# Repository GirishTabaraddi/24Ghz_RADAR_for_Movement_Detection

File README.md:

# 24Ghz_RADAR_for_Movement_Detection

This Project describes the Movement Detection using 24GHz CW-RADAR sensor which was performed in the System Driven Hardware Design Lab as a lab group.

KiCad_LabProject - This folder contains all the schematic and pcb files.
				 - 10_work folder contains the recent files of the project schematic.
				 - 20_release folder contains all the previous versions of the circuit design.

SDHD_PSoC_Codes - This folder contains all the project codes for various lab assigments and final code of the movement detector Project

SDHD_Lab3_FFT.cydsn - This workspace inside the SDHD_PSoC_Codes is the main code required for executing the Movement Detection.

Project Report pdf and ppt are added for reference to understand how the project was performed in the lab during summer semester.

This Project was carried at Hochschule Darmstadt during Summer semester 2023.
Other contributors are: Drashti Shah and Ananya Harish.

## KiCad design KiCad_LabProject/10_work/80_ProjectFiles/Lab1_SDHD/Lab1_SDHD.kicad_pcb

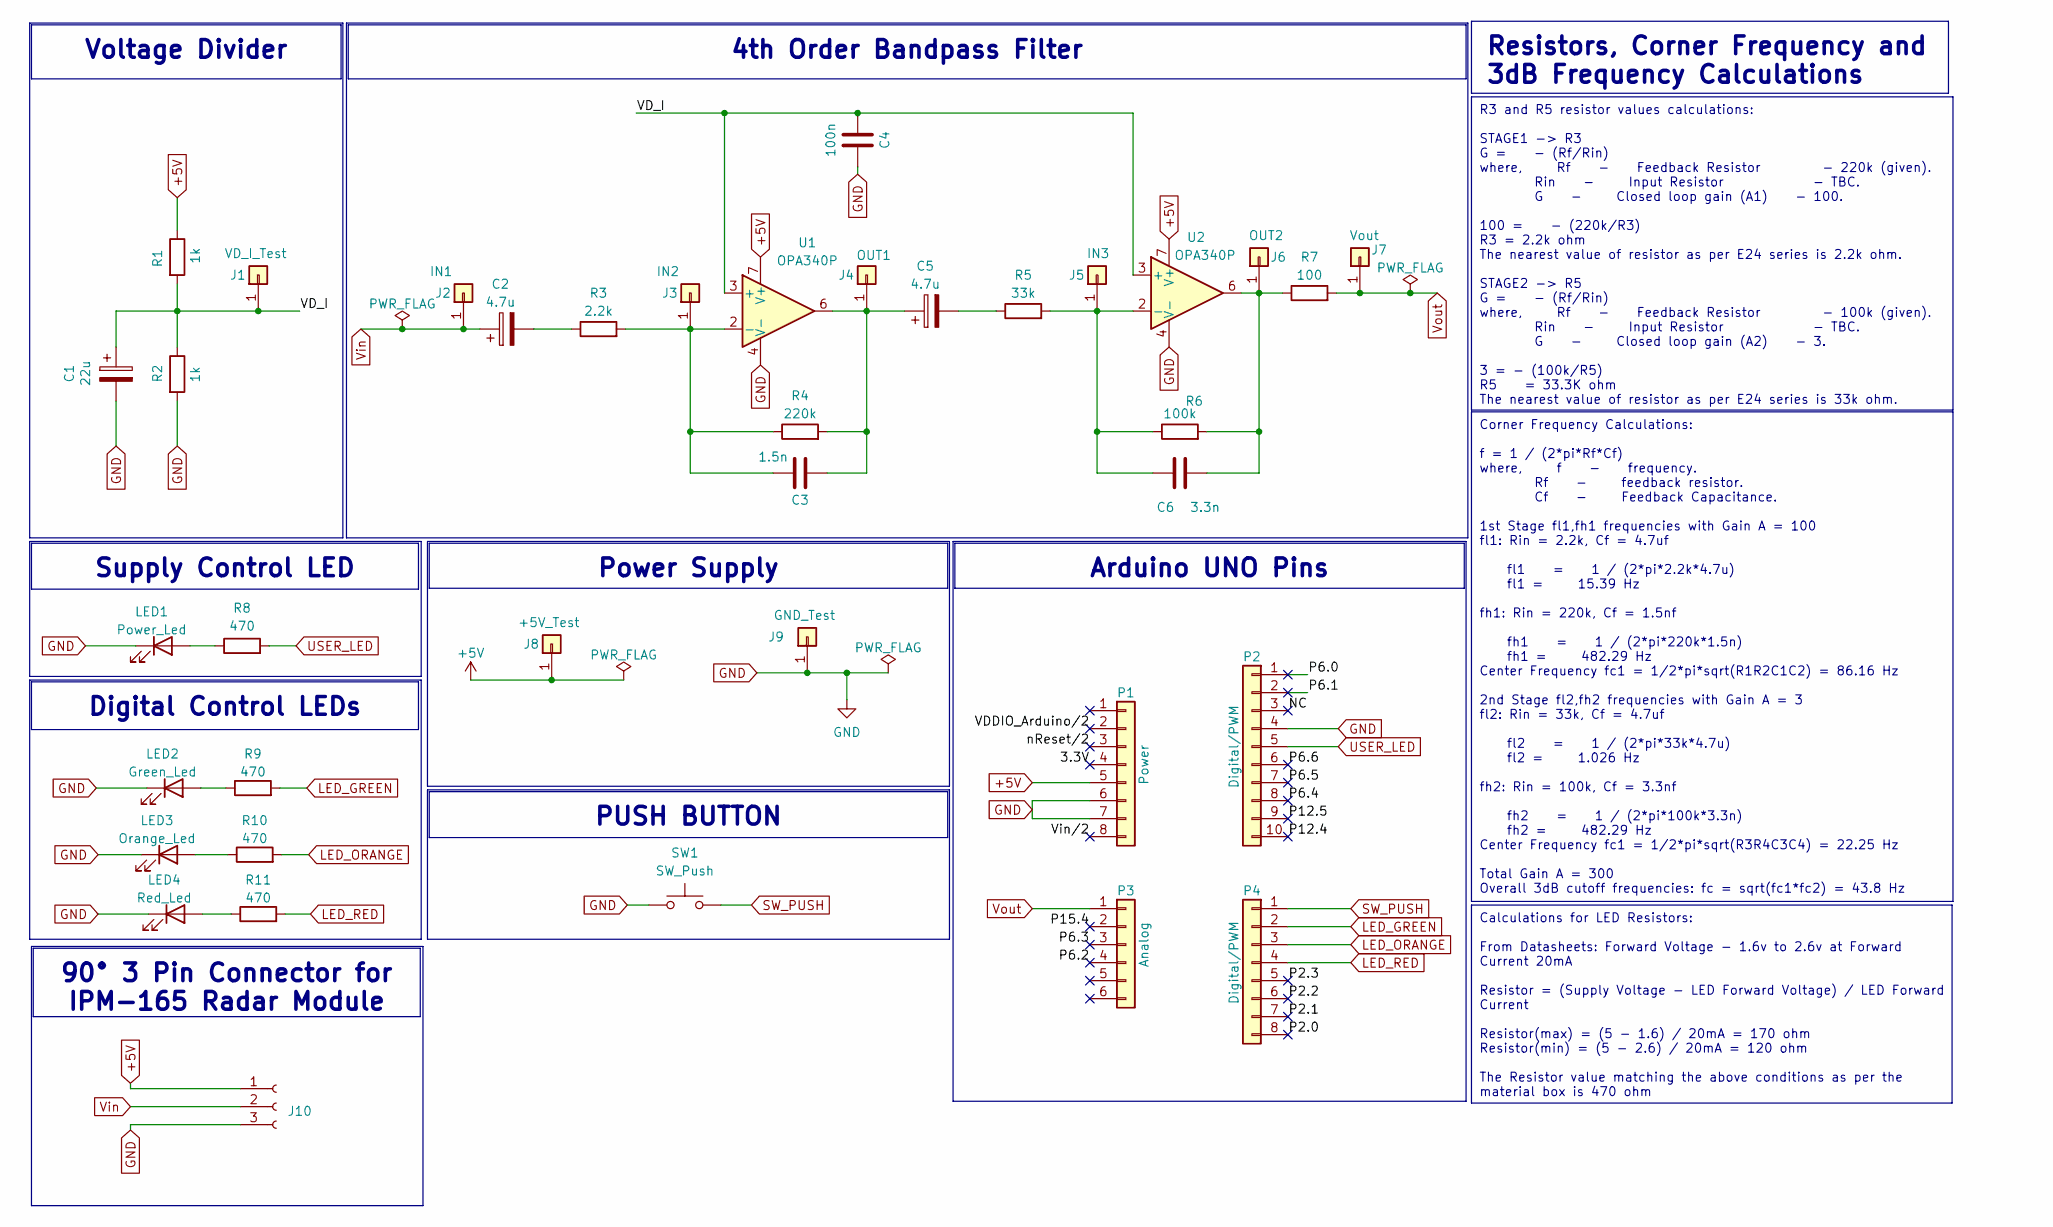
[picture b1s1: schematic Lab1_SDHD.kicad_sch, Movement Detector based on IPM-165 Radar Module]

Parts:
C1: 22u; CP_Radial_D5.0mm_P2.50mm
C2, C5: 4.7u; CP_Radial_D6.3mm_P2.50mm
C3: 1.5n; C_Rect_L7.2mm_W7.2mm_P5.00mm_FKS2_FKP2_MKS2_MKP2
C4: 100n; C_Rect_L7.2mm_W2.5mm_P5.00mm_FKS2_FKP2_MKS2_MKP2
C6: 3.3n; C_Rect_L7.2mm_W7.2mm_P5.00mm_FKS2_FKP2_MKS2_MKP2
J1: VD_I_Test; PinHeader_1x01_P2.54mm_Vertical
J2: IN1; PinHeader_1x01_P2.54mm_Vertical
J3: IN2; PinHeader_1x01_P2.54mm_Vertical
J4: OUT1; PinHeader_1x01_P2.54mm_Vertical
J5: IN3; PinHeader_1x01_P2.54mm_Vertical
J6: OUT2; PinHeader_1x01_P2.54mm_Vertical
J7: Vout; PinHeader_1x01_P2.54mm_Vertical
J8: +5V_Test; PinHeader_1x01_P2.54mm_Vertical
J9: GND_Test; PinHeader_1x01_P2.54mm_Vertical
J10: Conn_01x03_Socket; PinSocket_1x03_P2.54mm_Horizontal_NEW
LED1: Power_Led; LED_D5.0mm
LED2: Green_Led; LED_D5.0mm
LED3: Orange_Led; LED_D5.0mm
LED4: Red_Led; LED_D5.0mm
P1: Power; PinHeader_1x08_P2.54mm_Vertical
P2: Digital/PWM; PinHeader_1x10_P2.54mm_Vertical
P3: Analog; PinHeader_1x06_P2.54mm_Vertical
P4: Digital/PWM; PinHeader_1x08_P2.54mm_Vertical_New
R1, R2: 1k; R_Axial_DIN0207_L6.3mm_D2.5mm_P10.16mm_Horizontal
R3: 2.2k; R_Axial_DIN0207_L6.3mm_D2.5mm_P10.16mm_Horizontal
R4: 220k; R_Axial_DIN0207_L6.3mm_D2.5mm_P10.16mm_Horizontal
R5: 33k; R_Axial_DIN0207_L6.3mm_D2.5mm_P10.16mm_Horizontal
R6: 100k; R_Axial_DIN0207_L6.3mm_D2.5mm_P10.16mm_Horizontal
R7: 100; R_Axial_DIN0207_L6.3mm_D2.5mm_P10.16mm_Horizontal
R8, R9, R10, R11: 470; R_Axial_DIN0207_L6.3mm_D2.5mm_P10.16mm_Horizontal
SW1: SW_Push; SW_PUSH_6mm_H7.3mm
U1, U2: OPA340P; DIP-8_W7.62mm_Socket

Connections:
+5V: J8.1, J10.1, P1.5, R1.1, U1.7 (V+), U2.7 (V+)
/3.3V: P1.4
/NC: P2.3
/P2.0: P4.8
/P2.1: P4.7
/P2.2: P4.6
/P2.3: P4.5
/P6.0: P2.1
/P6.1: P2.2
/P6.2: P3.4
/P6.3: P3.3
/P6.4: P2.8
/P6.5: P2.7
/P6.6: P2.6
/P12.4: P2.10
/P12.5: P2.9
/P15.4: P3.2
/VDDIO_Arduino/2: P1.2
/VD_I: C1.1, C4.2, J1.1, R1.2, R2.1, U1.3 (+), U2.3 (+)
/Vin/2: P1.8
/nReset/2: P1.3
GND: C1.2, C4.1, J9.1, J10.3, LED1.1 (K), LED2.1 (K), LED3.1 (K), LED4.1 (K), P1.6, P1.7, P2.4, R2.2, SW1.1, U1.4 (V-), U2.4 (V-)
LED_GREEN: P4.2, R9.2
LED_ORANGE: P4.3, R10.2
LED_RED: P4.4, R11.2
unnamed: C2.2, R3.1
unnamed: C5.2, R5.1
unnamed: C3.1, J3.1, R3.2, R4.1, U1.2 (-)
unnamed: C3.2, C5.1, J4.1, R4.2, U1.6
unnamed: C6.1, J5.1, R5.2, R6.1, U2.2 (-)
unnamed: C6.2, J6.1, R6.2, R7.1, U2.6
unnamed: LED1.2 (A), R8.1
unnamed: LED2.2 (A), R9.1
unnamed: LED3.2 (A), R10.1
unnamed: LED4.2 (A), R11.1
SW_PUSH: P4.1, SW1.2
USER_LED: P2.5, R8.2
Vin: C2.1, J2.1, J10.2
Vout: J7.1, P3.1, R7.2

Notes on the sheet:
Power Supply
90° 3 Pin Connector for IPM-165 Radar Module
R3 and R5 resistor values calculations: STAGE1 -> R3 G = - (Rf/Rin) where, Rf - Feedback Resistor - 220k (given). Rin - Input Resistor - TBC. G - Closed loop gain (A1) - 100. 100 = - (220k/R3) R3 = 2.2k ohm The nearest value of resistor as per E24 series is 2.2k ohm. STAGE2 -> R5 G = - (Rf/Rin) whe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
Arduino UNO Pins
Corner Frequency Calculations: f = 1 / (2*pi*Rf*Cf) where, f - frequency. Rf - feedback resistor. Cf - Feedback Capacitance. 1st Stage fl1,fh1 frequencies with Gain A = 100 fl1: Rin = 2.2k, Cf = 4.7uf fl1 = 1 / (2*pi*2.2k*4.7u) fl1 = 15.39 Hz fh1: Rin = 220k, Cf = 1.5nf fh1 = 1 / (2*pi*220k*1.5n) f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
Calculations for LED Resistors: From Datasheets: Forward Voltage - 1.6v to 2.6v at Forward Current 20mA Resistor = (Supply Voltage - LED Forward Voltage) / LED Forward Current Resistor(max) = (5 - 1.6) / 20mA = 170 ohm Resistor(min) = (5 - 2.6) / 20mA = 120 ohm The Resistor value matching the above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
4th Order Bandpass Filter
Voltage Divider
Resistors, Corner Frequency and 3dB Frequency Calculations
Supply Control LED
Digital Control LEDs
PUSH BUTTON

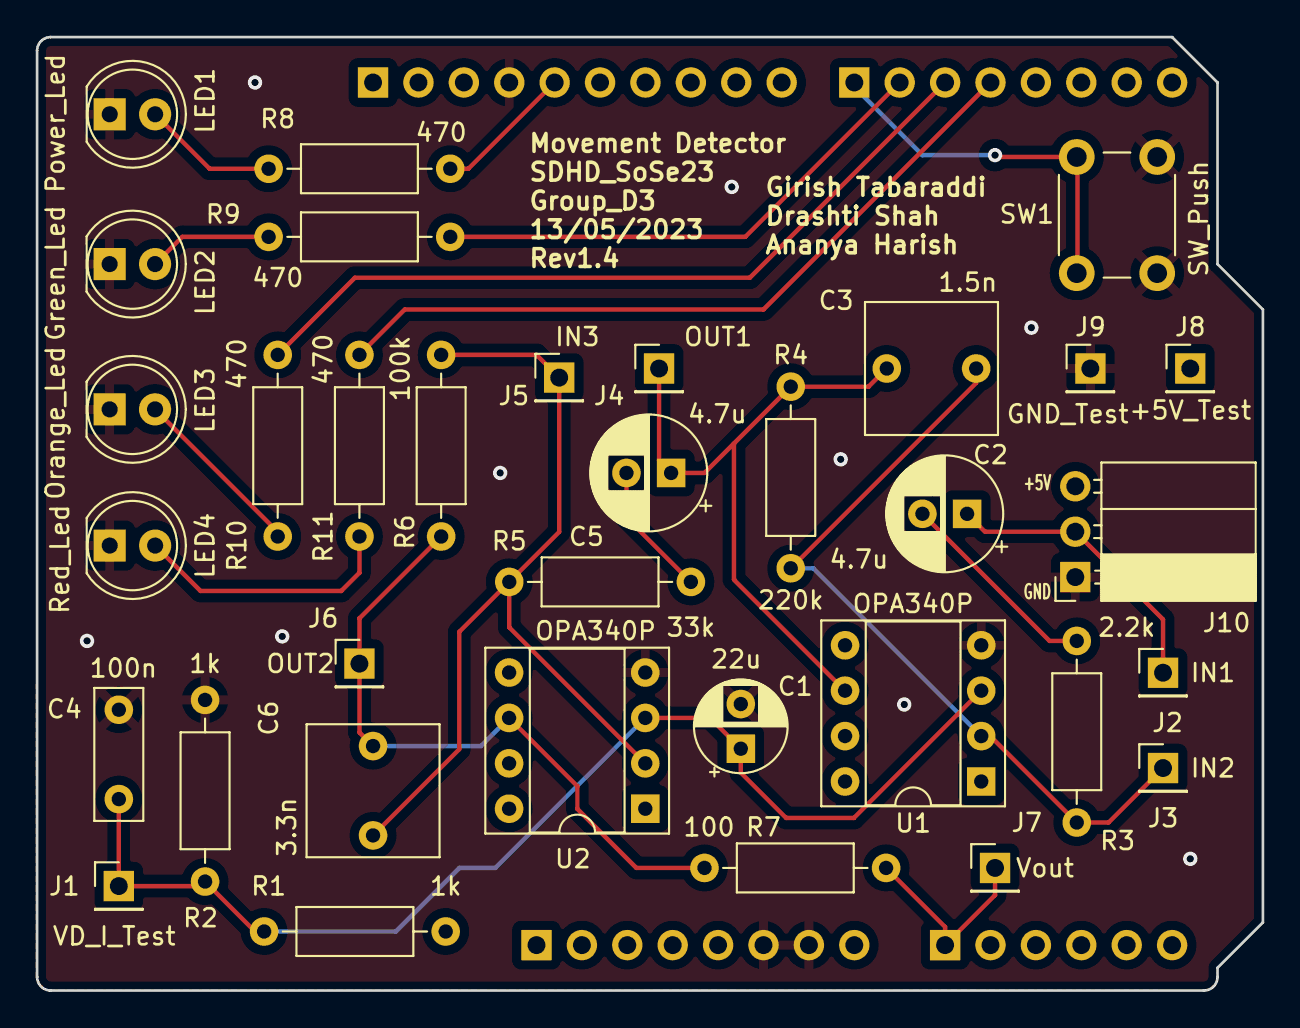
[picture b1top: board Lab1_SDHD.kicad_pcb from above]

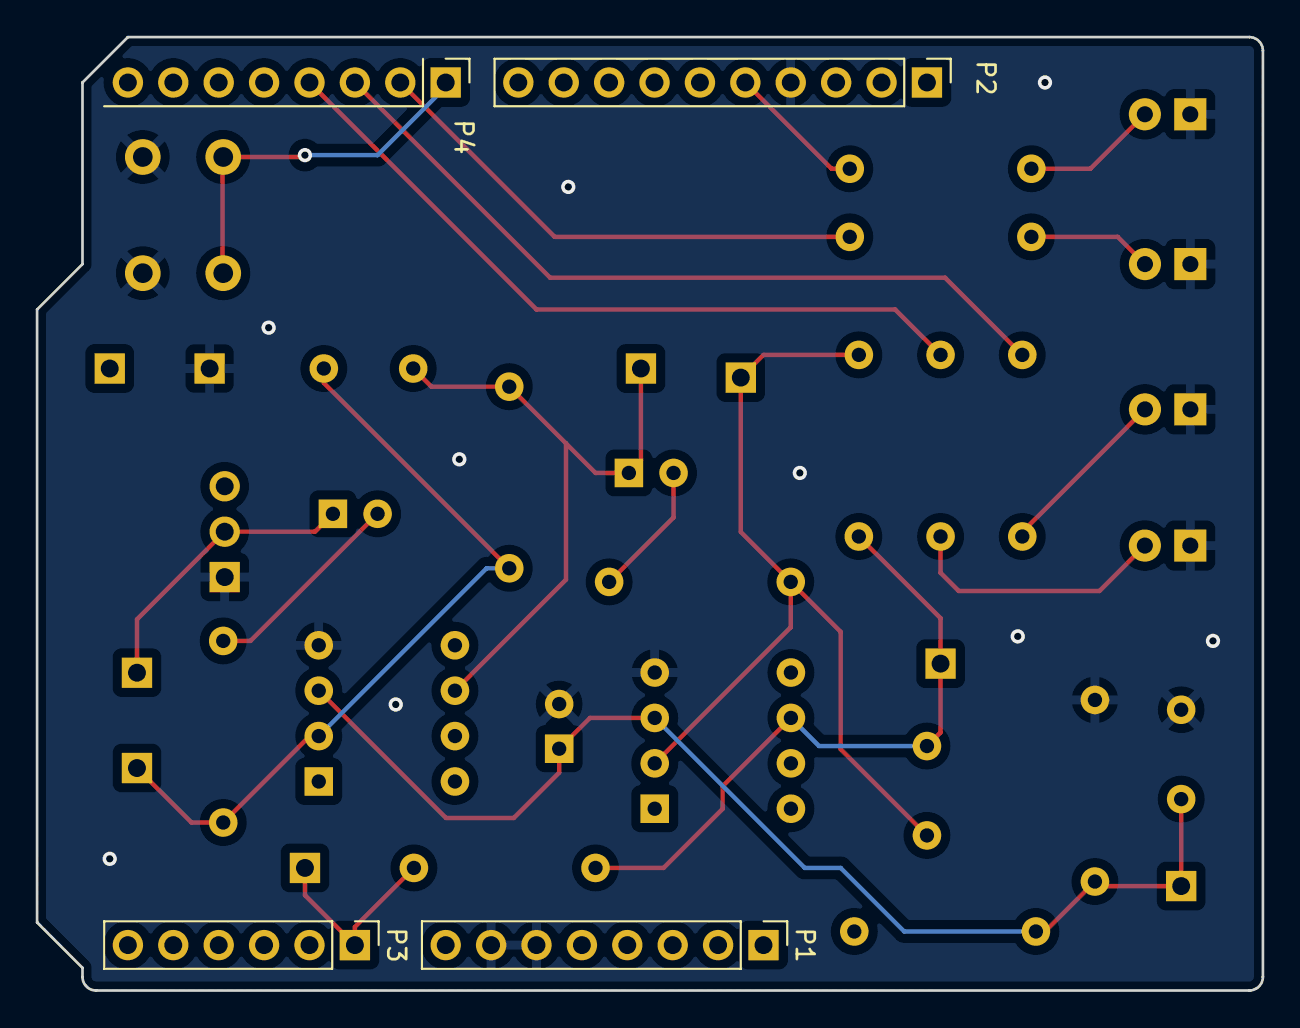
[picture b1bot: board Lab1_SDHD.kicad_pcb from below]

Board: 4 copper layers, 68.6 x 53.3 mm, 38 parts (4 on the bottom side), 20 nets.

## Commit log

2023-08-28 adding Kicad files to the feature branch
2023-08-28 adding psoc project codes to the feature branch
2023-08-28 adding matlab scripts to the new branch
2023-08-28 adding reports and ppt of the project
2023-08-28 modifying readme file
